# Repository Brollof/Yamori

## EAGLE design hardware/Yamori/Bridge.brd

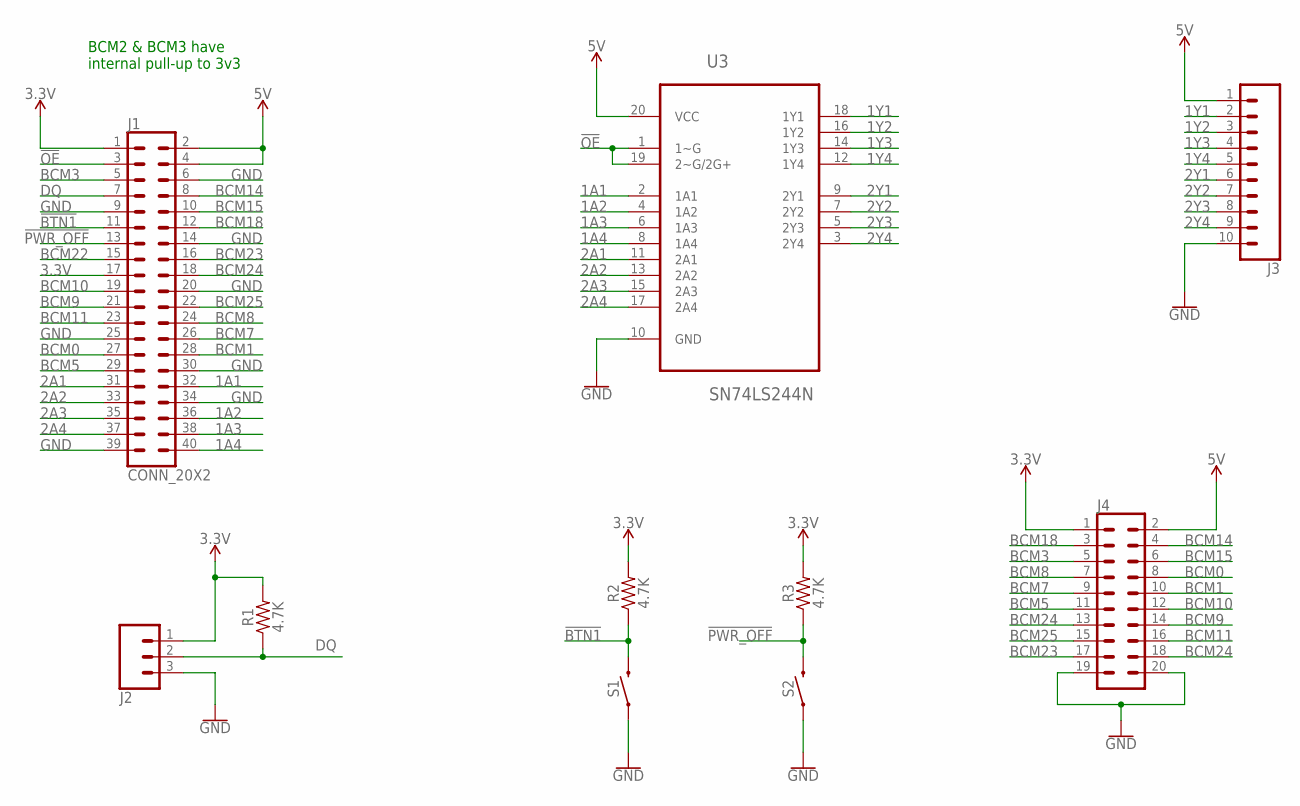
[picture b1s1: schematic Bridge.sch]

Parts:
J1: CONN_20X2; 2X20
J2: CONN_03-SCREW-5MM; SCREWTERMINAL-5MM-3
J3: CONN_10"; 1X10
J4: CONN_10X2; 2X10
R1, R2, R3: 4.7K; AXIAL-0.3
S1, S2: MOMENTARY-SWITCH-SPST-PTH-6.0MM; TACTILE_SWITCH_PTH_6.0MM
U3: SN74LS244N; DIP254P762X508-20

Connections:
1A1: J1.32, U3.2 (1A1)
1A2: J1.36, U3.4 (1A2)
1A3: J1.38, U3.6 (1A3)
1A4: J1.40, U3.8 (1A4)
1Y1: J3.2, U3.18 (1Y1)
1Y2: J3.3, U3.16 (1Y2)
1Y3: J3.4, U3.14 (1Y3)
1Y4: J3.5, U3.12 (1Y4)
2A1: J1.31, U3.11 (2A1)
2A2: J1.33, U3.13 (2A2)
2A3: J1.35, U3.15 (2A3)
2A4: J1.37, U3.17 (2A4)
2Y1: J3.6, U3.9 (2Y1)
2Y2: J3.7, U3.7 (2Y2)
2Y3: J3.8, U3.5 (2Y3)
2Y4: J3.9, U3.3 (2Y4)
3.3V: J1.1, J1.17, J2.1, J4.1, R1.P$2 (2), R2.P$2 (2), R3.P$2 (2)
5V: J1.2, J1.4, J3.1, J4.2, U3.20 (VCC)
!BTN1: J1.11, R2.P$1 (1), S1.3 (2)
!OE: J1.3, U3.1 (1~G), U3.19 (2~G/2G+)
!PWR_OFF: J1.13, R3.P$1 (1), S2.3 (2)
BCM0: J1.27, J4.8
BCM1: J1.28, J4.10
BCM3: J1.5, J4.5
BCM5: J1.29, J4.11
BCM7: J1.26, J4.9
BCM8: J1.24, J4.7
BCM9: J1.21, J4.14
BCM10: J1.19, J4.12
BCM11: J1.23, J4.16
BCM14: J1.8, J4.4
BCM15: J1.10, J4.6
BCM18: J1.12, J4.3
BCM23: J1.16, J4.17
BCM25: J1.22, J4.15
DQ: J1.7, J2.2, R1.P$1 (1)
GND: J1.6, J1.9, J1.14, J1.20, J1.25, J1.30, J1.34, J1.39, J2.3, J3.10, J4.19, J4.20, S1.1, S2.1, U3.10 (GND)

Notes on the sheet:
BCM2 & BCM3 have internal pull-up to 3v3

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
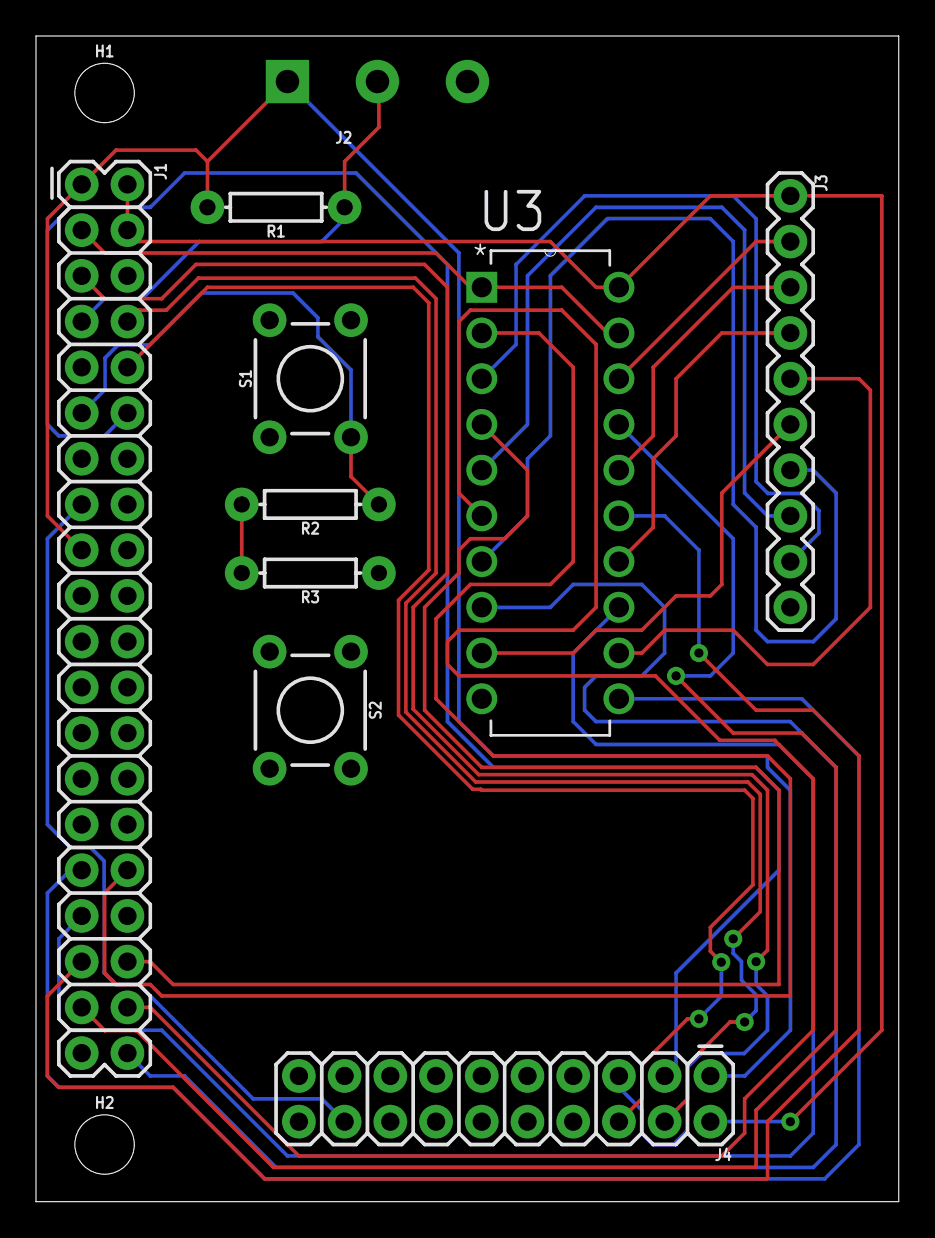
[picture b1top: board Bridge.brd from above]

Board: 2 copper layers, 47.9 x 64.8 mm, 12 parts (1 on the bottom side), 39 nets.

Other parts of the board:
H1, H2: STAND-OFF

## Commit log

2018-02-06 init
2018-02-06 pyqt working template
2018-02-06 GUI IO mockup
2018-02-06 Added ter_io.py missing file
2018-02-06 White background, buttons have border radius
2018-02-07 Logger working
2018-02-07 Added function for logging program termination
2018-02-08 Logging to stdout and *.log file
2018-02-08 Minor improvements
2018-02-08 New GUI design in progress
2018-02-12 Communication between server and pc app established
2018-02-15 New gui in progress - manual
2018-02-17 Heater icons added. Need refactor
2018-02-18 Icons cleanup
2018-02-18 Added diag and auto icons
2018-02-19 Status view filled.
2018-02-19 Small gui size fix.
2018-02-19 Menu indicator added.
2018-02-19 Menu indicator code cleanup.
2018-02-19 Code clean. Methods for reading IO added.
2018-02-19 GUI color adjusted
2018-02-19 Min temperature GUI controls added.
2018-02-25 Updating diagnostic page from separate thread
2018-02-26 New status icon. IO manager template.
2018-03-01 IO r/w thread safe - huge refactor
2018-03-02 Ignore list updated
2018-03-04 Gitignore updated. Linux setup updated.
2018-03-04 Read IO improved
2018-03-04 IO connected with GUI
2018-03-07 Instructions for setting up python3.5 with pyqt5 updated
2018-03-17 IO cross-platform. After HW check.
2018-03-17 Temp sensor datasheed added. System setup readme updated.
2018-03-24 IO refactor
2018-03-26 Reading temperature from sensors
2018-03-26 Updating GUI with real temperature values
2018-03-26 Cross-platform fixes
2018-04-17 Cross-platform fixes, gitignore update
2018-04-17 deleted lld
2018-04-17 Deleted tasks.txt
2018-04-23 Configurator project added. Connection between devices established.
2018-04-23 Creating sample JSON on the client side, sending, receiving & parsing on the server side.
2018-05-01 cleanup
2018-05-01 .gitignore update
2018-05-01 Timeline integrated (not fully functional yet)
2018-05-04 suo file added to ignore list
2018-05-04 Calendar code moved to separate file
2018-05-04 Comments removed
2018-05-04 Calendar view adjusted
2018-05-04 Now indicator removed
2018-05-04 All hours have the same color
2018-05-06 Events overlapping disabled
2018-05-06 Events tooltip changed. Added checkbox to show/hide time periods on events
2018-05-06 Creating config json
2018-05-06 Minor bug fix
2018-05-06 Color highlighting timelines
2018-05-06 Creating json from timeline data
2018-05-07 Small timeline color chosing refactor
2018-05-07 Dumping invalid time. Sorting event list ascending (by time)
2018-05-07 Concatenating events (not fully tested yet).
2018-05-07 Concatenating events on GUI before creating JSON
2018-05-08 List sorting function now returns list instead of passing variable by reference
2018-05-08 Workaround for additional period from next day implemented
2018-05-08 Workaround simplified
2018-05-08 Bug fixed where new event could be created on existing one
2018-05-09 Handling period which is split by midnight
2018-05-09 Adding lamp picker (WIP)
2018-05-09 Added missing file
2018-05-14 Added controls for defining lamps color and name
2018-05-14 Showing lamp picker improved
2018-05-15 Timeline rows manipulation
2018-05-15 Timeline row names are set
2018-05-20 Custom color dropdown list implemented
2018-05-21 Checking if given lamps names are valid
2018-05-21 Added JSON config field. Code clean.
2018-05-23 Heater timeline added
2018-05-23 Initializing heater row (name + color)
2018-05-23 Controls renamed
2018-05-23 Connection simplified
2018-05-29 Limit window added, table layout fully working
2018-05-29 LimitTempView: objects init changed
2018-06-02 Limit window minor improvements
2018-06-02 ViewModel logic refactored
2018-06-02 Added controls for setting max and min temp limits
2018-06-02 Max temp limit removed
2018-06-02 TempLimit: removed first empty column
2018-06-02 TempLimit: col width changing improved
2018-06-02 Project structure changed. Limit window size adjusted (fixed)
2018-06-02 TempLimit: textbox width adjusted
2018-06-02 NumericTextBox introduced
2018-06-02 TempLimit: fields validation added
2018-06-02 TempLimit: heater column added
2018-06-02 LimitTemp: controls centered
2018-06-02 Limit window width increased
2018-06-02 Updating correctly data on Limit window
2018-06-04 Min and max temp correct update
2018-06-04 App crash after increasing devices num bug fixed. RMB context menu translated properly
2018-06-04 Limit temp added to JSON
2018-06-04 Enabling send button fixed.
2018-06-04 Dropdown list read only
2018-06-05 Version 1.0
2018-06-05 Diagnostic module created. Link thread added.
2018-06-05 Added method for showing init screen
2018-06-06 Saving received JSON to file
2018-06-06 Added functions for save reading and writing json files
2018-06-06 ter_utils renamed. Settings module added.
2018-06-06 Minor logging changes
2018-06-06 Logging bug fixed
2018-06-06 After socket QThread vs Thread battle...
2018-06-10 Huge refactor: device model introduced (replaces old pseudo-devices)
2018-06-10 Slot number presented on timelines
2018-06-11 Remove device context menu added
2018-06-11 Hiding timeline when there are no devices to show
2018-06-11 Removing device model
2018-06-11 Cannot add device with already used slot id
2018-06-11 Cannot add device with already used name
2018-06-11 Added description for controls in device add group
2018-06-11 Type field in JSON frame changed
2018-06-11 Invisible color label at startup bug fixed
2018-06-18 Config refactor. GUI buttons temporarily disabled
2018-06-19 Updating GUI buttons with received config data
2018-06-20 Event handler added. Link data rcv len increased to 8k
2018-06-22 Json deserializing test
2018-06-22 Retrieving limit config from json
2018-06-22 Updating timeline from JSON...
2018-06-22 A few bug fixes
2018-06-22 Date removed from events, only time is important
2018-06-23 Reading data from JSON finished
2018-06-23 Reading JSON from RPI
2018-06-23 Bug fixed where removing timeline rows didn't resize the window
2018-06-23 Limit temp window update after receive JSON data bug fixed
2018-06-23 Bug with event ended at midnight fixed
2018-06-30 Proper event handling
2018-06-30 Auto events now update GUI buttons
2018-07-01 event_handler: all properties as private
2018-07-09 Checking temp limits
2018-07-09 GUI clicker added - code refactor
2018-11-08 main cleanup
2018-11-10 Crossplatform fixes
2018-11-10 Tools added: cpu temp logger
2018-11-11 hostname used instead of ip address
2018-11-11 Mlem: limits disabled
2018-11-11 Main application running in fullscreen mode
2018-11-11 Mlem build to single exe file
2018-11-11 Added main app startup script
2018-11-11 cpu temp tool: fixed logging to file
2018-11-11 Tool for getting max CPU temperature from log file
2018-11-12 power on fixes
2018-11-12 Other type devices than lamp and cable are no longer triggering GUI
2018-11-12 Including missing ddl files into Mlem.exe
2018-11-13 Delay after devices reinit added
2018-11-13 Socket rcv on the host side fix
2018-11-13 linux setup update
2018-11-14 Pins for devices changed
2018-11-14 Script for setting backlight added
2018-11-18 Temperature refactor, CPU temp on GUI
2018-11-20 cpu temp testing fixes
2018-11-20 LCD diagnostic scripts
2018-12-03 HW bridge project added
2018-12-03 Holes removed
2018-12-05 Schema final version
2018-12-05 Wiring in progress
2019-01-15 expander datasheet added

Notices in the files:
parts and their libraries:
SparkFun-Connectors: Licensing: Creative Commons ShareAlike 4.0 International - https://creativecommons.org/licenses/by-sa/4.0
